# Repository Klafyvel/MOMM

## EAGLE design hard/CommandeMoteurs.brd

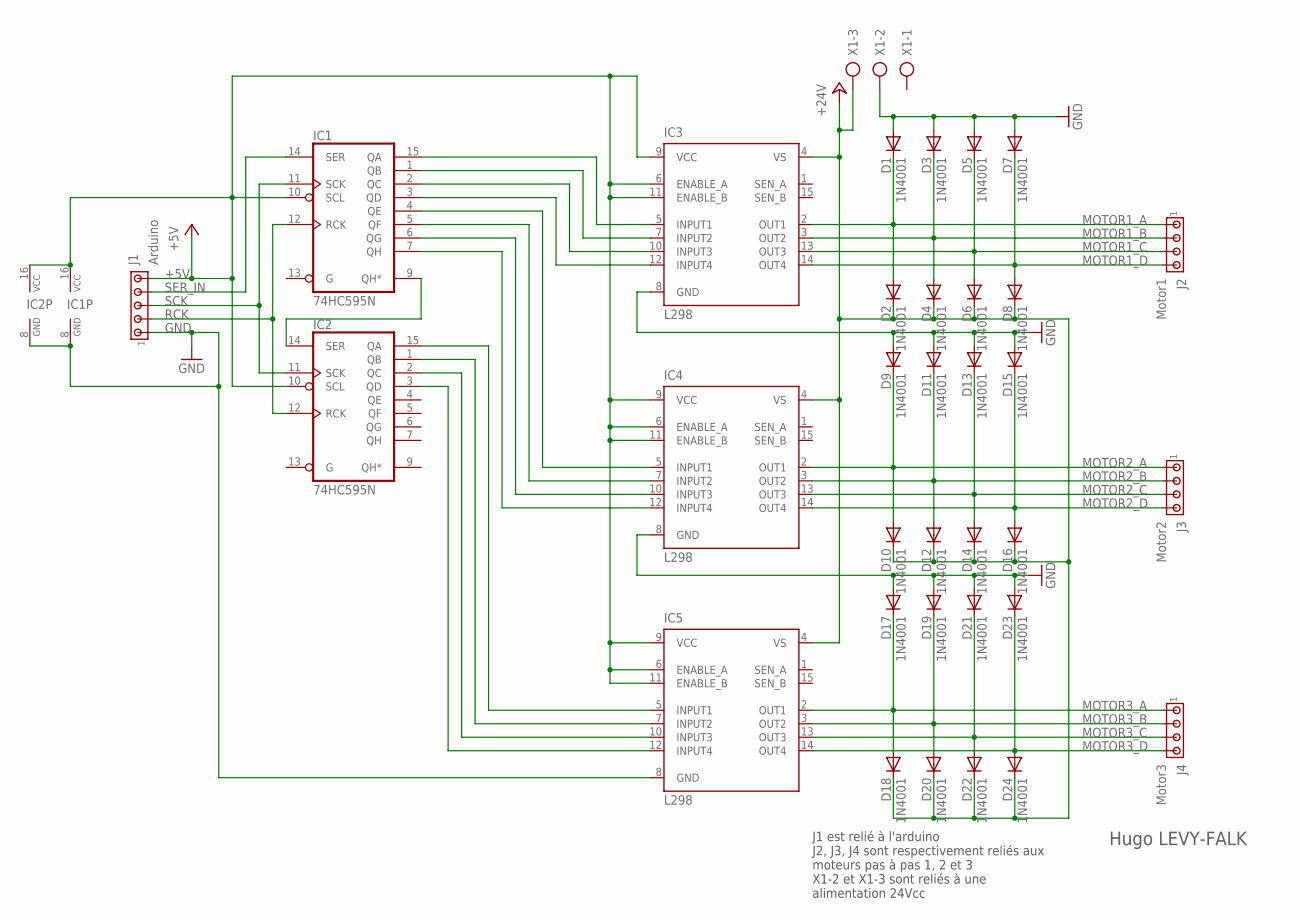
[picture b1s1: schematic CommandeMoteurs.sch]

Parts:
D1, D2, D3, D4, D5, D6, D7, D8, D9, D10, D11, D12, D13, D14, D15, D16, D17, D18, D19, D20, D21, D22, D23, D24: 1N4001; DO35-10
IC1, IC2: 74HC595N; DIL16
IC3, IC4, IC5: L298; MULTIWATT-15
J1: Arduino; 10X05MTA
J2: Motor1; 10X04MTA
J3: Motor2; 10X04MTA
J4: Motor3; 10X04MTA
X1: AK500/3

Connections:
+5V: IC1.10 (SCL), IC1.16 (VCC), IC2.10 (SCL), IC2.16 (VCC), IC3.6 (ENABLE_A), IC3.9 (VCC), IC3.11 (ENABLE_B), IC4.6 (ENABLE_A), IC4.9 (VCC), IC4.11 (ENABLE_B), IC5.6 (ENABLE_A), IC5.9 (VCC), IC5.11 (ENABLE_B), J1.5
+24V: D2.C, D4.C, D6.C, D8.C, D10.C, D12.C, D14.C, D16.C, D18.C, D20.C, D22.C, D24.C, IC3.4 (VS), IC4.4 (VS), IC5.4 (VS), X1.3
GND: D1.A, D3.A, D5.A, D7.A, D9.A, D11.A, D13.A, D15.A, D17.A, D19.A, D21.A, D23.A, IC1.8 (GND), IC2.8 (GND), IC3.8 (GND), IC4.8 (GND), IC5.8 (GND), J1.1, X1.2
MOTOR1_A: D1.C, D2.A, IC3.2 (OUT1), J2.1
MOTOR1_B: D3.C, D4.A, IC3.3 (OUT2), J2.2
MOTOR1_C: D5.C, D6.A, IC3.13 (OUT3), J2.3
MOTOR1_D: D7.C, D8.A, IC3.14 (OUT4), J2.4
MOTOR2_A: D9.C, D10.A, IC4.2 (OUT1), J3.1
MOTOR2_B: D11.C, D12.A, IC4.3 (OUT2), J3.2
MOTOR2_C: D13.C, D14.A, IC4.13 (OUT3), J3.3
MOTOR2_D: D15.C, D16.A, IC4.14 (OUT4), J3.4
MOTOR3_A: D17.C, D18.A, IC5.2 (OUT1), J4.1
MOTOR3_B: D19.C, D20.A, IC5.3 (OUT2), J4.2
MOTOR3_C: D21.C, D22.A, IC5.13 (OUT3), J4.3
MOTOR3_D: D23.C, D24.A, IC5.14 (OUT4), J4.4
unnamed: IC1.15 (QA), IC3.5 (INPUT1)
unnamed: IC1.1 (QB), IC3.7 (INPUT2)
unnamed: IC1.2 (QC), IC3.10 (INPUT3)
unnamed: IC1.3 (QD), IC3.12 (INPUT4)
unnamed: IC1.4 (QE), IC4.5 (INPUT1)
unnamed: IC1.5 (QF), IC4.7 (INPUT2)
unnamed: IC1.6 (QG), IC4.10 (INPUT3)
unnamed: IC1.7 (QH), IC4.12 (INPUT4)
unnamed: IC1.9 (QH*), IC2.14 (SER)
unnamed: IC2.15 (QA), IC5.5 (INPUT1)
unnamed: IC2.1 (QB), IC5.7 (INPUT2)
unnamed: IC2.2 (QC), IC5.10 (INPUT3)
unnamed: IC2.3 (QD), IC5.12 (INPUT4)
RCK: IC1.12 (RCK), IC2.12 (RCK), J1.2
SCK: IC1.11 (SCK), IC2.11 (SCK), J1.3
SER_IN: IC1.14 (SER), J1.4

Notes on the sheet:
J1 est relié à l'arduino J2, J3, J4 sont respectivement reliés aux moteurs pas à pas 1, 2 et 3 X1-2 et X1-3 sont reliés à une alimentation 24Vcc
Hugo LEVY-FALK

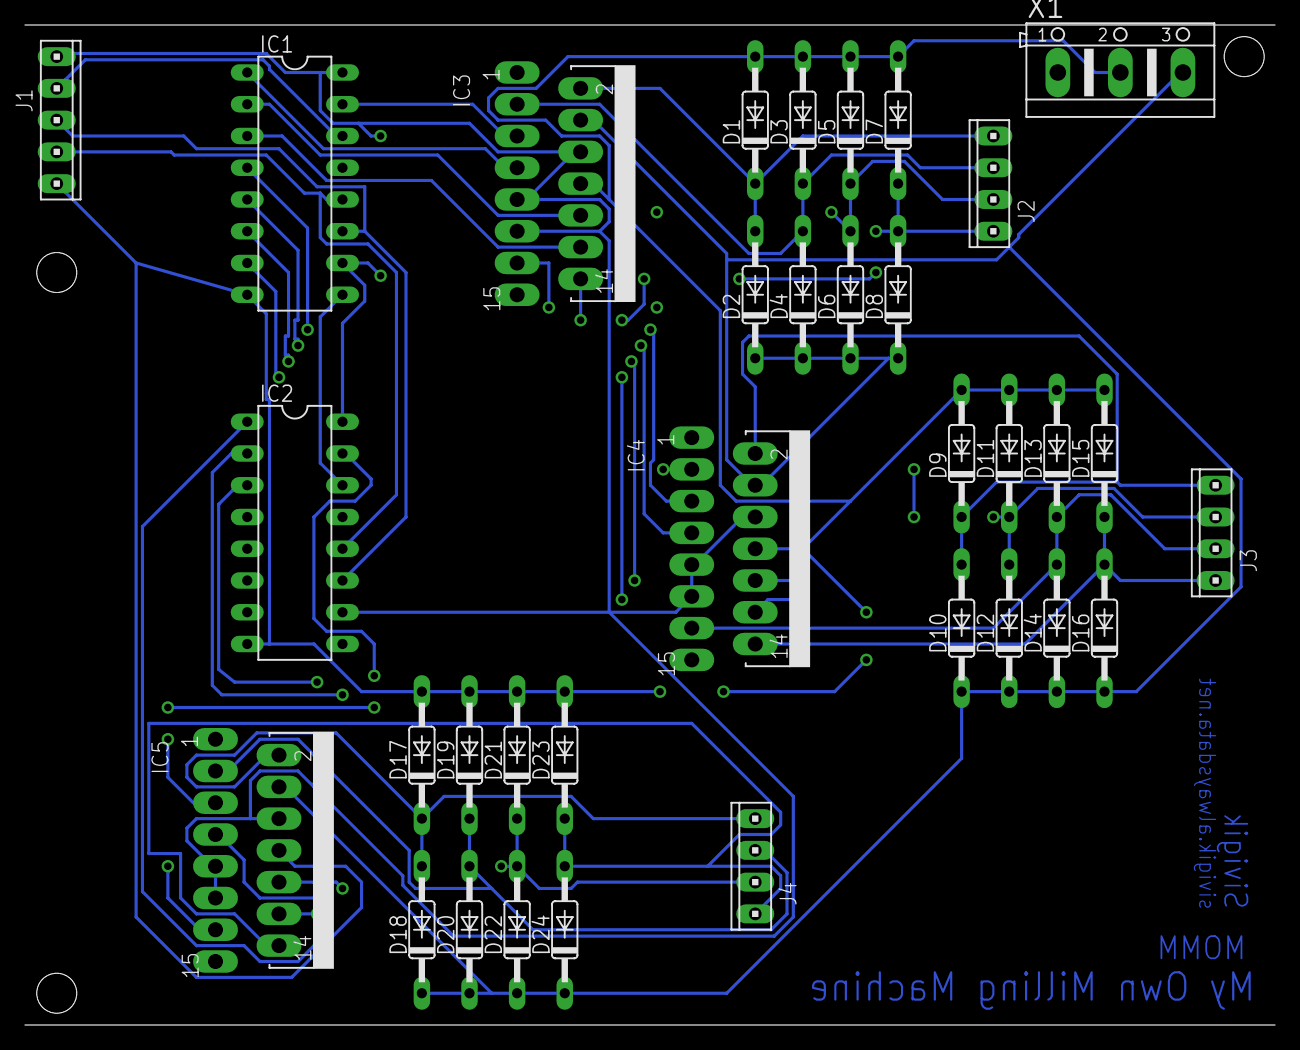
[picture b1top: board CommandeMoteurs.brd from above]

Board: 2 copper layers, 100.0 x 80.0 mm, 34 parts (0 on the bottom side), 31 nets.

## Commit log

2014-06-23 Mise à jour carte.
2014-06-23 Ajout des schémas pour la commande des moteurs.
2014-06-23 Mode demi pas sur le fichier de test.
2014-06-23 Ajout de fichiers pour extraire les commandes Gcodes les plus utilisées.
2014-06-23 Ajout des fichiers pour le contrôle de l'arduino.
2014-06-23 Ignore les fichiers de sublime text !
2014-07-20 Add: gcode analyser to know which command are the most used.
2014-07-20 Add: Axis displacment
2014-07-20 Began to implement gcode
2014-07-20 deleted gcode.cpp
2014-07-20 Update config
2014-07-20 Add: machine control
2014-07-24 begin of creating window for the gcode sender.
2014-08-02 gitignore !
2014-08-02 begin machine plans
2014-08-17 Changement dans l'organisation des sources.
2014-08-17 Ajout des bras et du tiroir ainsi que d'annotations.
